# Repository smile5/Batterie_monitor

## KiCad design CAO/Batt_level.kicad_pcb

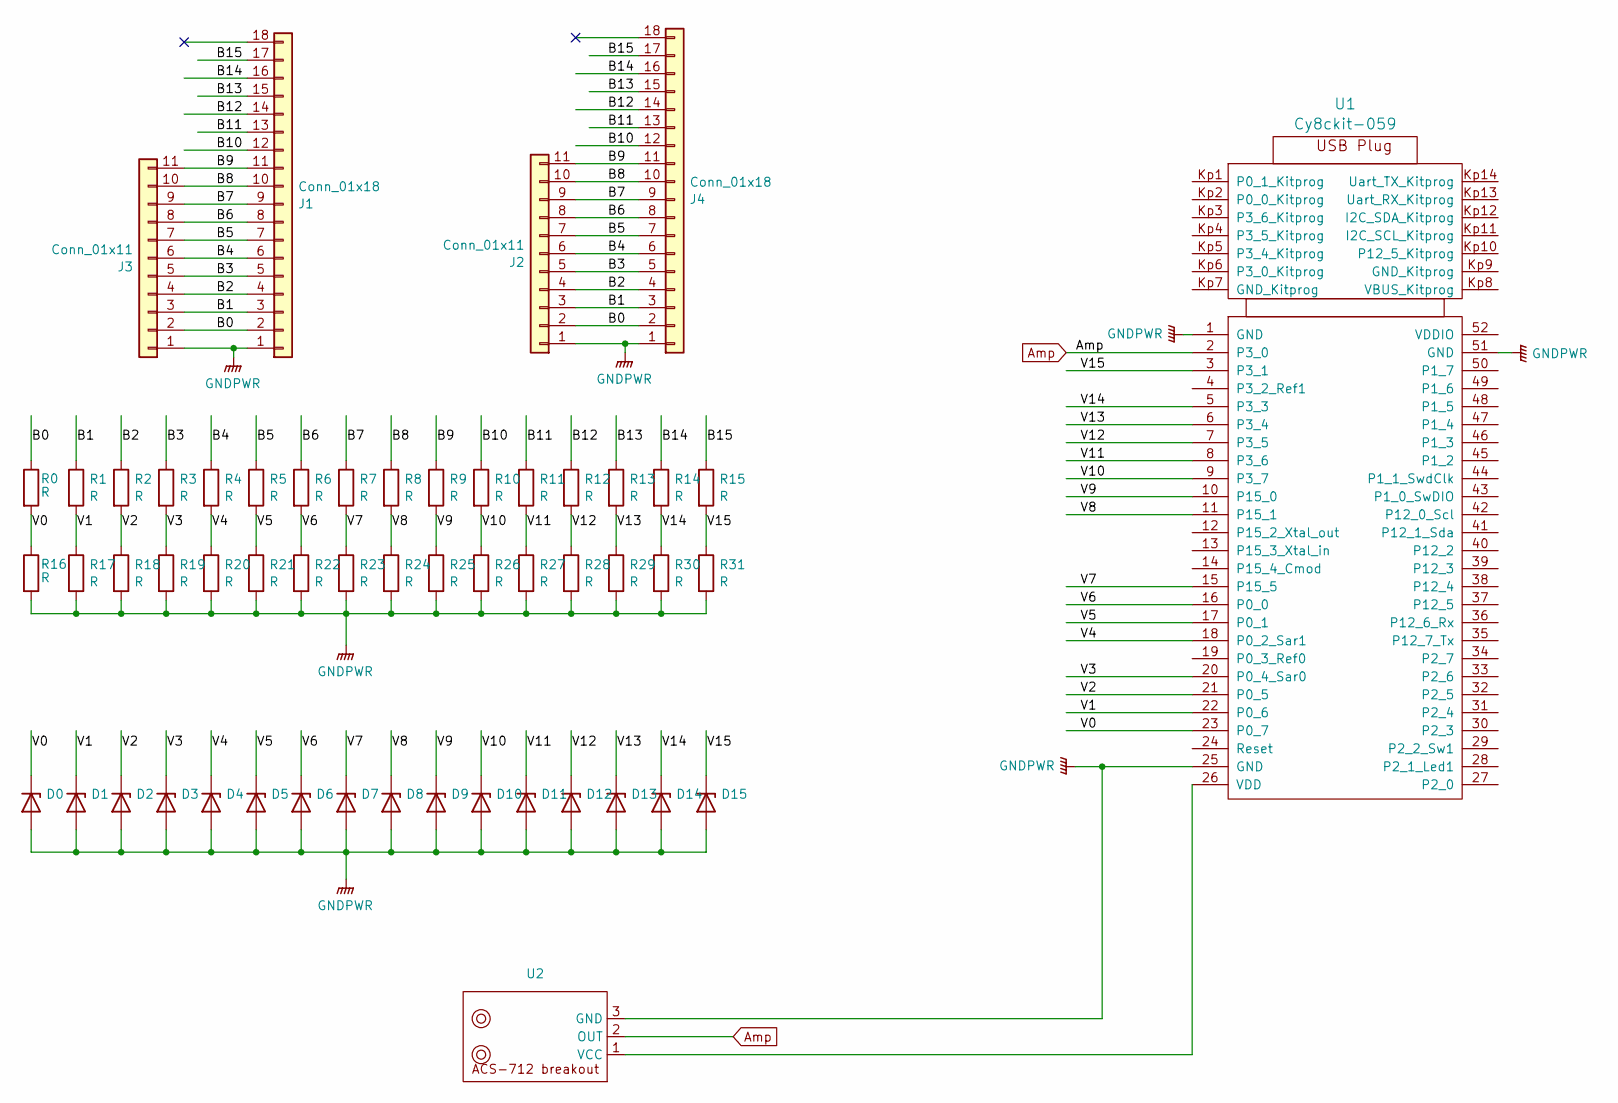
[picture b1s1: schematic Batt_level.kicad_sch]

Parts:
D0, D1, D2, D3, D4, D5, D6, D7, D8, D9, D10, D11, D12, D13, D14, D15: BZV55C3V6; D_DO-35_SOD27_P7.62mm_Horizontal
J1, J4: Conn_01x18; PinHeader_1x18_P2.54mm_Vertical
J2, J3: Conn_01x11; PinHeader_1x11_P2.54mm_Vertical
R0, R1, R2, R3, R4, R5, R6, R7, R8, R9, R10, R11, R12, R13, R14, R15, R16, R17, R18, R19, R20, R21, R22, R23, R24, R25, R26, R27, R28, R29, R30, R31: R; R_Axial_DIN0207_L6.3mm_D2.5mm_P10.16mm_Horizontal
U1: Cy8ckit-059
U2: ACS-712_breakout

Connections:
/B0: J1.2, J2.2, J3.2, J4.2, R0.1
/B1: J1.3, J2.3, J3.3, J4.3, R1.1
/B2: J1.4, J2.4, J3.4, J4.4, R2.1
/B3: J1.5, J2.5, J3.5, J4.5, R3.1
/B4: J1.6, J2.6, J3.6, J4.6, R4.1
/B5: J1.7, J2.7, J3.7, J4.7, R5.1
/B6: J1.8, J2.8, J3.8, J4.8, R6.1
/B7: J1.9, J2.9, J3.9, J4.9, R7.1
/B8: J1.10, J2.10, J3.10, J4.10, R8.1
/B9: J1.11, J2.11, J3.11, J4.11, R9.1
/B10: J1.12, J4.12, R10.1
/B11: J1.13, J4.13, R11.1
/B12: J1.14, J4.14, R12.1
/B13: J1.15, J4.15, R13.1
/B14: J1.16, J4.16, R14.1
/B15: J1.17, J4.17, R15.1
/V0: D0.1 (K), R0.2, R16.1, U1.23 (P0_7)
/V1: D1.1 (K), R1.2, R17.1, U1.22 (P0_6)
/V2: D2.1 (K), R2.2, R18.1, U1.21 (P0_5)
/V3: D3.1 (K), R3.2, R19.1, U1.20 (P0_4_Sar0)
/V4: D4.1 (K), R4.2, R20.1, U1.18 (P0_2_Sar1)
/V5: D5.1 (K), R5.2, R21.1, U1.17 (P0_1)
/V6: D6.1 (K), R6.2, R22.1, U1.16 (P0_0)
/V7: D7.1 (K), R7.2, R23.1, U1.15 (P15_5)
/V8: D8.1 (K), R8.2, R24.1, U1.11 (P15_1)
/V9: D9.1 (K), R9.2, R25.1, U1.10 (P15_0)
/V10: D10.1 (K), R10.2, R26.1, U1.9 (P3_7)
/V11: D11.1 (K), R11.2, R27.1, U1.8 (P3_6)
/V12: D12.1 (K), R12.2, R28.1, U1.7 (P3_5)
/V13: D13.1 (K), R13.2, R29.1, U1.6 (P3_4)
/V14: D14.1 (K), R14.2, R30.1, U1.5 (P3_3)
/V15: D15.1 (K), R15.2, R31.1, U1.3 (P3_1)
Amp: U1.2 (P3_0), U2.2 (OUT)
GNDPWR: D0.2 (A), D1.2 (A), D2.2 (A), D3.2 (A), D4.2 (A), D5.2 (A), D6.2 (A), D7.2 (A), D8.2 (A), D9.2 (A), D10.2 (A), D11.2 (A), D12.2 (A), D13.2 (A), D14.2 (A), D15.2 (A), J1.1, J2.1, J3.1, J4.1, R16.2, R17.2, R18.2, R19.2, R20.2, R21.2, R22.2, R23.2, R24.2, R25.2, R26.2, R27.2, R28.2, R29.2, R30.2, R31.2, U1.1 (GND), U1.25 (GND), U1.51 (GND), U2.3 (GND)
unnamed: U1.26 (VDD), U2.1 (VCC)

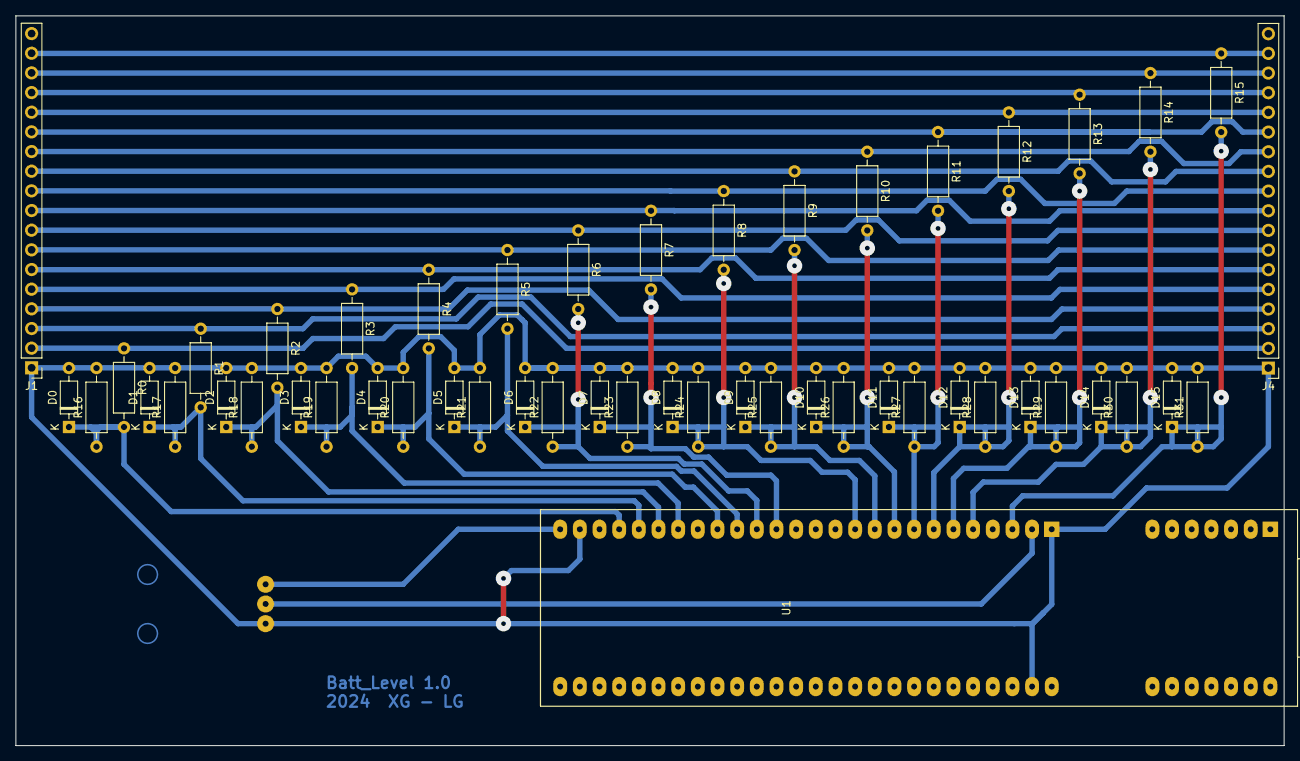
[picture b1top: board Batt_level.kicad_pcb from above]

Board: 2 copper layers, 163.8 x 94.3 mm, 52 parts (1 on the bottom side), 35 nets.
